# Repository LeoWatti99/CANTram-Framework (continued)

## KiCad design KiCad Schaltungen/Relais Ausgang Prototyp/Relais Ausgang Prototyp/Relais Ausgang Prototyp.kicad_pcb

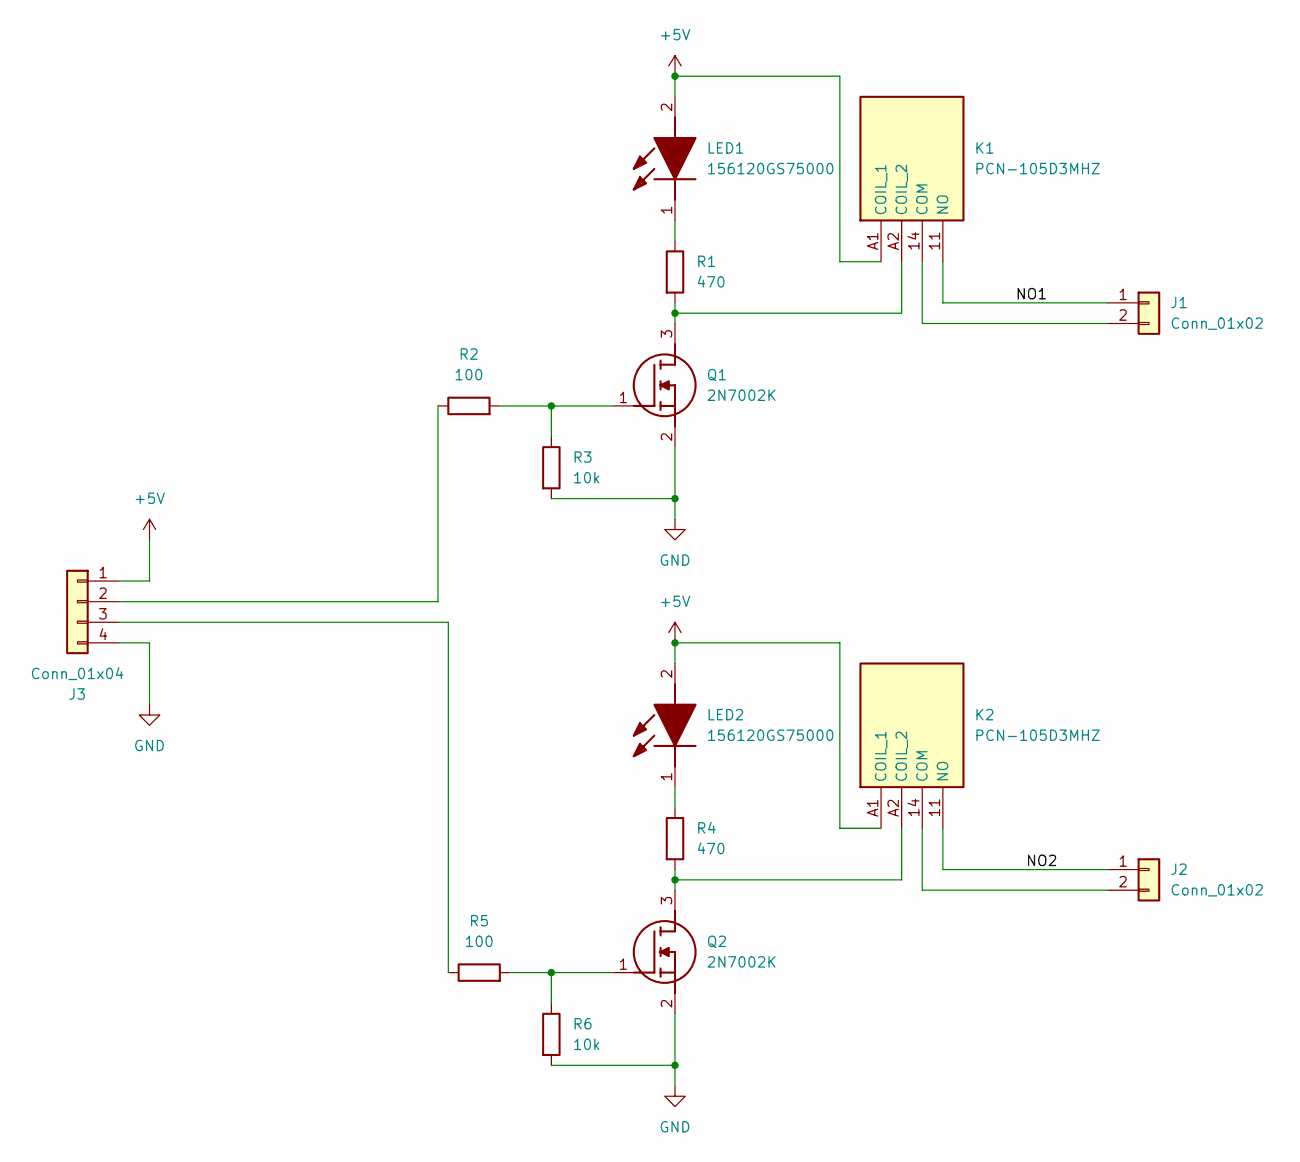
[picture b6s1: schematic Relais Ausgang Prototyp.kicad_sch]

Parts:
J1, J2: Conn_01x02; PinHeader_1x02_P2.54mm_Vertical
J3: Conn_01x04; PinHeader_1x04_P2.54mm_Vertical
K1, K2: PCN-105D3MHZ; PCN105D3MHZ; Mouser Part Number 677-PCN-105D3MHZ
LED1, LED2: 156120GS75000; Mouser Part Number 710-156120GS75000
Q1, Q2: 2N7002K; SOT95P240X120-3N; Manufacturer_Part_Number 2N7002K; Mouser Part Number 512-2N7002K
R1, R4: 470; R_1206_3216Metric; Manufacturer_Part_Number AC1206FR-07470RL; Mouser Part Number 603-AC1206FR-07470RL
R2, R5: 100; R_1206_3216Metric; Manufacturer_Part_Number AC1206FR-07100RL; Mouser Part Number 603-AC1206FR-07100RL
R3, R6: 10k; R_1206_3216Metric; Manufacturer_Part_Number RC1206FR-1310KL; Mouser Part Number 603-RC1206FR-1310KL

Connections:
+5V: J3.1, K1.A1 (COIL_1), K2.A1 (COIL_1), LED1.2 (A), LED2.2 (A)
/NO1: J1.1, K1.11 (NO)
/NO2: J2.1, K2.11 (NO)
GND: J3.4, Q1.2 (S), Q2.2 (S), R3.2, R6.2
unnamed: J1.2, K1.14 (COM)
unnamed: J2.2, K2.14 (COM)
unnamed: J3.2, R2.1
unnamed: J3.3, R5.1
unnamed: K1.A2 (COIL_2), Q1.3 (D), R1.2
unnamed: K2.A2 (COIL_2), Q2.3 (D), R4.2
unnamed: LED1.1 (K), R1.1
unnamed: LED2.1 (K), R4.1
unnamed: Q1.1 (G), R2.2, R3.1
unnamed: Q2.1 (G), R5.2, R6.1

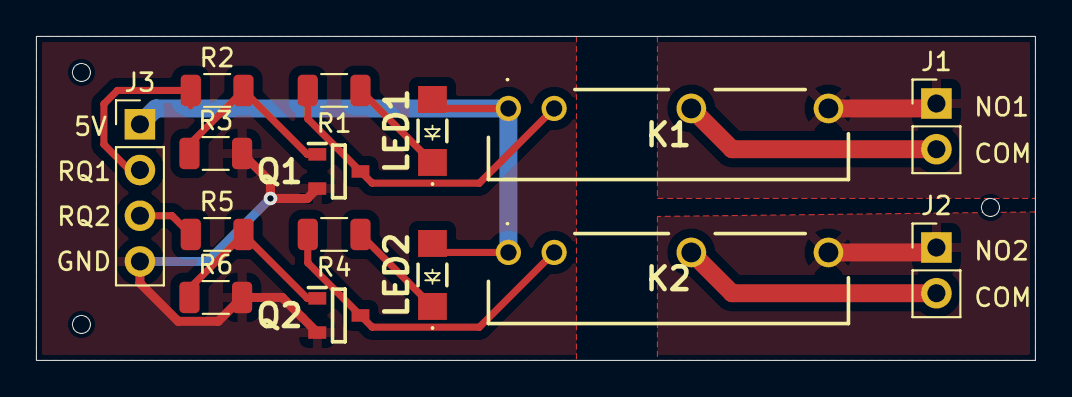
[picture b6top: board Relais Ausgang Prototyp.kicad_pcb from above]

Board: 2 copper layers, 55.5 x 18.0 mm, 15 parts (0 on the bottom side), 14 nets.

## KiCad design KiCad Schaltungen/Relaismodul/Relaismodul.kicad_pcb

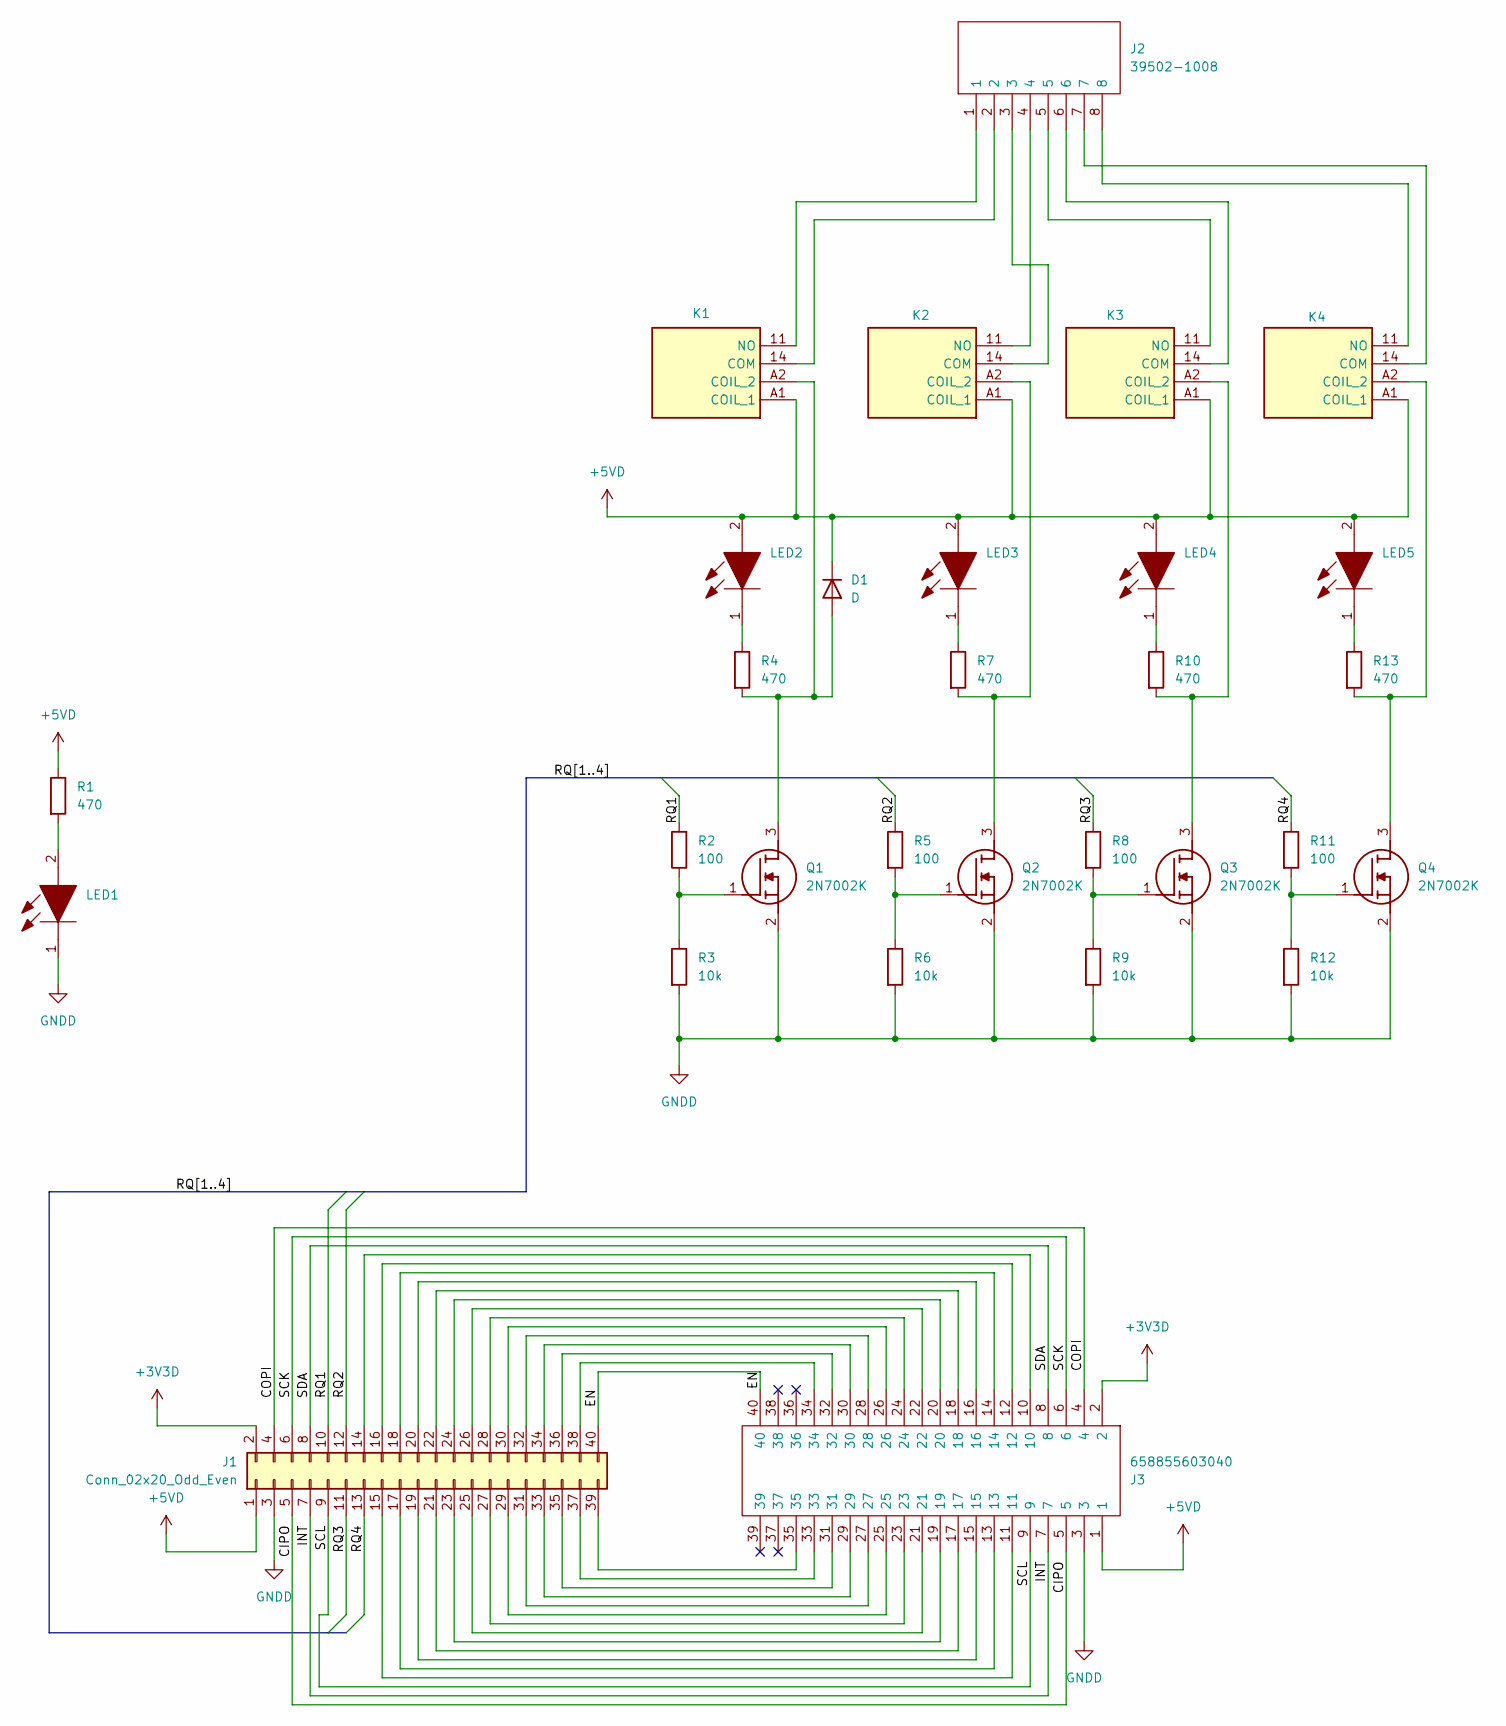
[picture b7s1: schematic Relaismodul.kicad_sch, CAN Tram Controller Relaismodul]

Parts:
D1: D
J1: Conn_02x20_Odd_Even; PinSocket_2x20_P2.54mm_Vertical
J2: 39502-1008; SHDRRA8W80P0X350_1X8_2940X920X690P; Mouser Part Number 538-39502-1008
J3: 658855603040; Mouser Part Number 710-658855603040
K1, K2, K3, K4: PCN-105D3MHZ; PCN105D3MHZ; Mouser Part Number 677-PCN-105D3MHZ
LED1: 156120GS75000; Mouser Part Number 710-156120GS75000
LED2, LED3, LED4, LED5: 156120YS75000; LEDC5017X140N; Mouser Part Number 710-156120YS75000
Q1, Q2, Q3, Q4: 2N7002K; SOT95P240X120-3N; Manufacturer_Part_Number 2N7002K; Mouser Part Number 512-2N7002K
R1, R4, R7, R10, R13: 470; R_1206_3216Metric; Manufacturer_Part_Number AC1206FR-07470RL; Mouser Part Number 603-AC1206FR-07470RL
R2, R5, R8, R11: 100; R_1206_3216Metric; Manufacturer_Part_Number AC1206FR-07100RL; Mouser Part Number 603-AC1206FR-07100RL
R3, R6, R9, R12: 10k; R_1206_3216Metric; Manufacturer_Part_Number RC1206FR-1310KL; Mouser Part Number 603-RC1206FR-1310KL

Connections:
+3V3D: J1.2, J3.2
+5VD: D1.1 (K), J1.1, J3.1, K1.A1 (COIL_1), K2.A1 (COIL_1), K3.A1 (COIL_1), K4.A1 (COIL_1), LED2.2, LED3.2, LED4.2, LED5.2, R1.1
/CIPO: J1.5, J3.5
/COPI: J1.4, J3.4
/EN: J1.40, J3.40
/INT: J1.7, J3.7
/RQ1: J1.10, R2.2
/RQ2: J1.12, R5.1
/RQ3: J1.11, R8.1
/RQ4: J1.13, R11.1
/SCK: J1.6, J3.6
/SCL: J1.9, J3.9
/SDA: J1.8, J3.8
GNDD: J1.3, J3.3, LED1.1, Q1.2 (S), Q2.2 (S), Q3.2 (S), Q4.2 (S), R3.2, R6.2, R9.2, R12.2
unnamed: J1.14, J3.10
unnamed: J1.15, J3.11
unnamed: J1.16, J3.12
unnamed: J1.17, J3.13
unnamed: J1.18, J3.14
unnamed: J1.19, J3.15
unnamed: J1.20, J3.16
unnamed: J1.21, J3.17
unnamed: J1.22, J3.18
unnamed: J1.23, J3.19
unnamed: J1.24, J3.20
unnamed: J1.25, J3.21
unnamed: J1.26, J3.22
unnamed: J1.27, J3.23
unnamed: J1.28, J3.24
unnamed: J1.29, J3.25
unnamed: J1.30, J3.26
unnamed: J1.31, J3.27
unnamed: J1.32, J3.28
unnamed: J1.33, J3.29
unnamed: J1.34, J3.30
unnamed: J1.35, J3.31
unnamed: J1.36, J3.32
unnamed: J1.37, J3.33
unnamed: J1.38, J3.34
unnamed: J1.39, J3.35
unnamed: D1.2 (A), K1.A2 (COIL_2), Q1.3 (D), R4.2
unnamed: J2.2, K1.14 (COM)
unnamed: J2.1, K1.11 (NO)
unnamed: K2.A2 (COIL_2), Q2.3 (D), R7.2
unnamed: J2.3, K2.14 (COM)
unnamed: J2.4, K2.11 (NO)
unnamed: K3.A2 (COIL_2), Q3.3 (D), R10.2
unnamed: J2.6, K3.14 (COM)
unnamed: J2.5, K3.11 (NO)
unnamed: K4.A2 (COIL_2), Q4.3 (D), R13.2
unnamed: J2.7, K4.14 (COM)
unnamed: J2.8, K4.11 (NO)
unnamed: LED1.2, R1.2
unnamed: LED2.1, R4.1
unnamed: LED3.1, R7.1
unnamed: LED4.1, R10.1
unnamed: LED5.1, R13.1
unnamed: Q1.1 (G), R2.1, R3.1
unnamed: Q2.1 (G), R5.2, R6.1
unnamed: Q3.1 (G), R8.2, R9.1
unnamed: Q4.1 (G), R11.2, R12.1

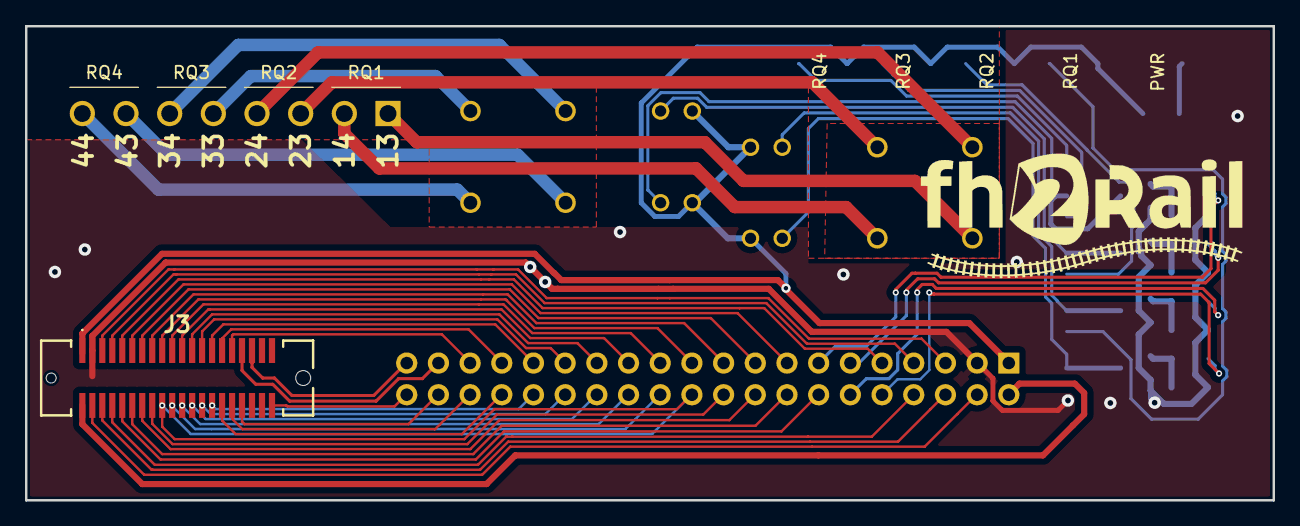
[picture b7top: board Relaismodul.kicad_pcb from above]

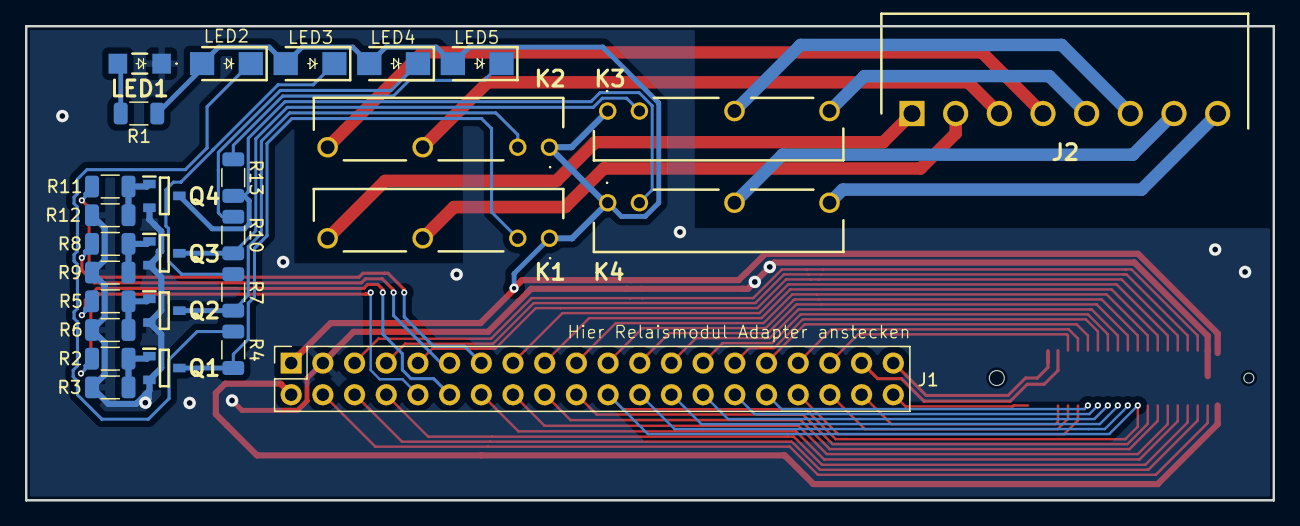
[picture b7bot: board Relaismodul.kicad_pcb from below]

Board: 2 copper layers, 100.0 x 38.0 mm, 29 parts (28 on the bottom side), 61 nets.
